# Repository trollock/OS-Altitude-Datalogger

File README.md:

Note: version 3.0.0 is undergoing revision, merge of version 4.0.0 expected November 2018. It is strongly advised to await improvements in v 4.0.0.

# OS-Altitude-Datalogger
Open Source Code and Design Files for the TI MSP430FR5949 and Bosch BME280 Altitude Datalogger

The following repository contains the drivers, software, and EAGLE files to create a low power datalogger capable of recording pressure, temperature, and (with modified software) humidity. 

# About the BME280
(https://ae-bst.resource.bosch.com/media/_tech/media/datasheets/BST-BME280_DS001-11.pdf) 

# About the MSP430FR5969
The MSP430FR596 is an ultra-low power MCU capable of recording up to 64 kB of data to non-volatile FRAM memory.  FRAM (ferro-magnetic Random Access Memory) has advantages over other memory types such as flash by requiring significantly less power and faster write times.
(http://www.ti.com/product/MSP430FR5949)

# To install
Dowload this repository as a zip
Unzip file and rename to "MSP430FR5949_LP"
Locate the Folder where the Energia applicaiton is installed
Copy this folder into the following directory: /Contents/Resources/Java/hardware/msp430/variants/
Open the boards.txt file located at: /Contents/Resources/Java/hardware/msp430/ in a text editor
Append the following text at the end of the file

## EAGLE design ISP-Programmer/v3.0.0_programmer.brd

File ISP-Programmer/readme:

The follwing files are for the PCB to program dataloggers on a MSP430FR5969 Launchpad vis ISP

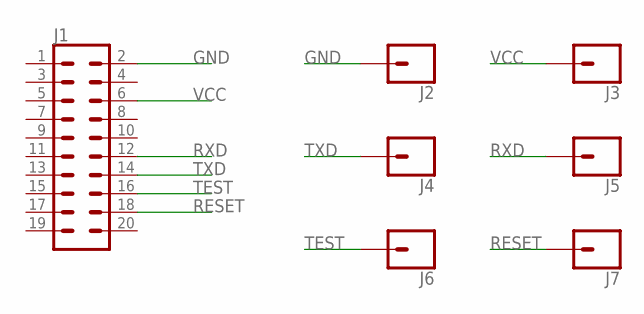
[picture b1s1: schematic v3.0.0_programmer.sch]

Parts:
J1: CONN_10X2NOSILK; 2X10_NOSILK
J2, J3, J4, J5, J6, J7: CONN_01; 1X01

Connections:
GND: J1.2, J2.1
RESET: J1.18, J7.1
RXD: J1.12, J5.1
TEST: J1.16, J6.1
TXD: J1.14, J4.1
VCC: J1.6, J3.1

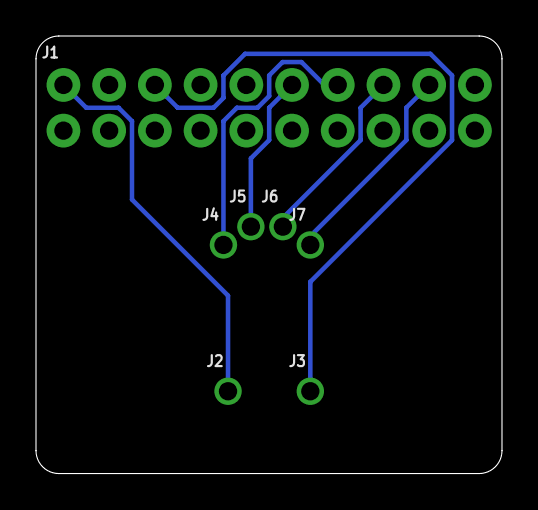
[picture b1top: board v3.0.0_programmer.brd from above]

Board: 2 copper layers, 25.9 x 24.3 mm, 7 parts (0 on the bottom side), 6 nets.

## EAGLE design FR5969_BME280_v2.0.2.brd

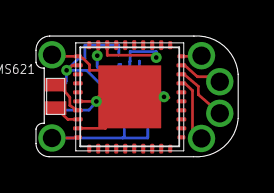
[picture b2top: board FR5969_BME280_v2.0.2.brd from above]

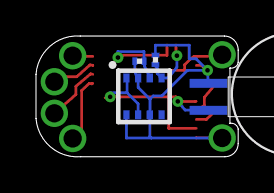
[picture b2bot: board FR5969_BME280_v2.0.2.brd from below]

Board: 2 copper layers, 11.2 x 6.7 mm, 12 parts (3 on the bottom side), 10 nets.

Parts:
J1: VSS; 1X01
J2: VCC; 1X01
J3: TXD; 1X01
J4: RXD; 1X01
J5: TEST; 1X01
J6: RESET; 1X01
R1, R2: 4.7k; R0201
U1: BME280; BME280_LGA
U$1: MSP430FR5949_RHA; RHA-40-VQFN
U$2: ABS06; 2.0X1.0RTC
U$3: SEIKO-MS621; SEIKO_MICRO

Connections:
RESET: J6.1, U$1.20
RXD: J4.1, U$1.18
SCL: R2.2, U1.P$4, U$1.29
SDA: R1.2, U1.P$3, U$1.28
TEST: J5.1, U$1.19
TXD: J3.1, U$1.17
VCC: J2.1, R1.1, R2.1, U1.P$2, U1.P$6, U1.P$8, U$1.32, U$1.40, U$3.1-POS
VSS: J1.1, U1.P$1, U1.P$7, U$1.31, U$1.36, U$1.39, U$3.2-GND
XTAL_IN: U$1.37, U$2.2-XTI
XTAL_OUT: U$1.38, U$2.1-XTO

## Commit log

2017-05-29 Create MSP430FR5949_LP

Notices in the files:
parts and their libraries:
SparkFun-Connectors: Licensing: Creative Commons ShareAlike 4.0 International - https://creativecommons.org/licenses/by-sa/4.0
